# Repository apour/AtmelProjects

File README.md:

"# AtmelProjects" 
Zmena v souboru readme

Zmena vsouboru do master branch

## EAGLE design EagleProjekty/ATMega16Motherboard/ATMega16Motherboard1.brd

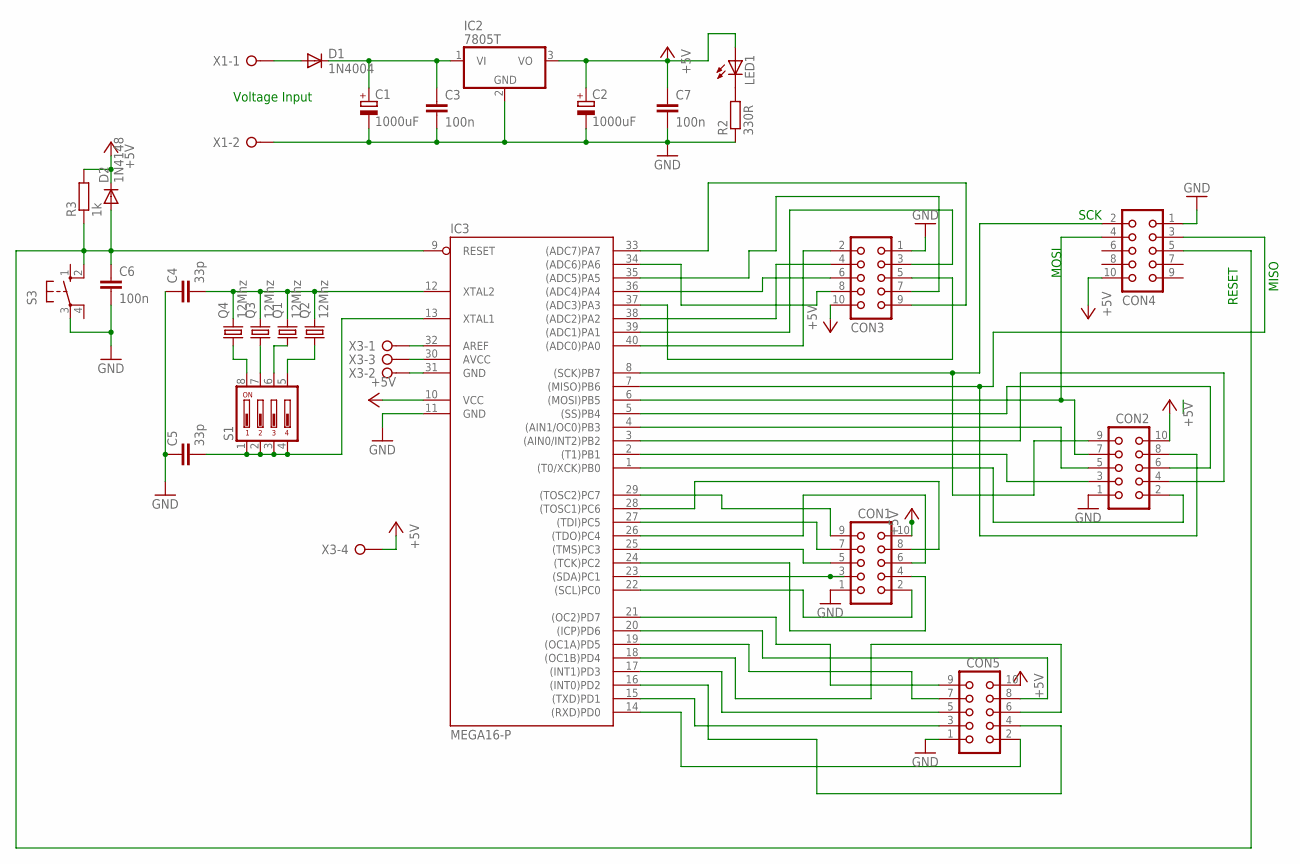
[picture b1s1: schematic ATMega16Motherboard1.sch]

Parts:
C1, C2: 1000uF; E2,5-7
C3, C6, C7: 100n; C025-024X044
C4, C5: 33p; C025-024X044
CON1, CON2, CON3, CON4, CON5: CON10
D1: 1N4004; DO41-10
D2: 1N4148; DO35-10
IC2: 7805T; TO220H
IC3: MEGA16-P; DIL40
LED1: LED5MM
Q1, Q2, Q3, Q4: 12Mhz; HC18U-V
R2: 330R; 0204/5
R3: 1k; 0204/5
S1: DIP04YL
S3: 10-XX; B3F-10XX
X1: W237-02P; W237-132
X3: W237-04P; W237-4P

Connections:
+5V: C2.+, C7.1, CON1.10, CON2.10, CON3.10, CON4.10, CON5.10, D2.C, IC2.3 (VO), IC3.10 (VCC), LED1.A, R3.2, X3.4
GND: C1.-, C2.-, C3.2, C4.1, C5.1, C6.2, C7.2, CON1.1, CON2.1, CON3.1, CON4.1, CON5.1, IC2.2 (GND), IC3.11 (GND), R2.1, S3.3, X1.2
unnamed: D1.A, X1.1
unnamed: C1.+, C3.1, D1.C, IC2.1 (VI)
unnamed: CON1.2, IC3.22 ((SCL)PC0)
unnamed: CON2.2, IC3.1 ((T0/XCK)PB0)
unnamed: CON2.3, IC3.2 ((T1)PB1)
unnamed: CON1.3, IC3.23 ((SDA)PC1)
unnamed: IC3.32 (AREF), X3.1
unnamed: CON2.4, IC3.3 ((AIN0/INT2)PB2)
unnamed: CON2.5, IC3.4 ((AIN1/OC0)PB3)
unnamed: CON2.6, IC3.5 ((SS)PB4)
unnamed: CON3.2, IC3.40 ((ADC0)PA0)
unnamed: IC3.30 (AVCC), X3.3
unnamed: IC3.31 (GND), X3.2
unnamed: Q4.1, S1.8
unnamed: Q3.1, S1.7
unnamed: Q1.1, S1.6
unnamed: Q2.1, S1.5
unnamed: CON3.3, IC3.39 ((ADC1)PA1)
unnamed: CON1.4, IC3.24 ((TCK)PC2)
unnamed: LED1.K (C), R2.2
unnamed: CON2.9, CON4.2, IC3.8 ((SCK)PB7)
unnamed: CON2.7, CON4.4, IC3.6 ((MOSI)PB5)
unnamed: CON2.8, CON4.3, IC3.7 ((MISO)PB6)
unnamed: CON5.7, IC3.19 ((OC1A)PD5)
unnamed: C5.2, IC3.13 (XTAL1), S1.1, S1.2, S1.3, S1.4
unnamed: C4.2, IC3.12 (XTAL2), Q1.2, Q2.2, Q3.2, Q4.2
unnamed: C6.1, CON4.5, D2.A, IC3.9 (RESET), R3.1, S3.2 (S1)
unnamed: CON3.4, IC3.38 ((ADC2)PA2)
unnamed: CON3.5, IC3.37 ((ADC3)PA3)
unnamed: CON3.6, IC3.36 ((ADC4)PA4)
unnamed: CON3.7, IC3.35 ((ADC5)PA5)
unnamed: CON3.8, IC3.34 ((ADC6)PA6)
unnamed: CON3.9, IC3.33 ((ADC7)PA7)
unnamed: CON1.5, IC3.25 ((TMS)PC3)
unnamed: CON1.6, IC3.26 ((TDO)PC4)
unnamed: CON1.7, IC3.27 ((TDI)PC5)
unnamed: CON1.8, IC3.28 ((TOSC1)PC6)
unnamed: CON1.9, IC3.29 ((TOSC2)PC7)
unnamed: CON5.9, IC3.21 ((OC2)PD7)
unnamed: CON5.8, IC3.20 ((ICP)PD6)
unnamed: CON5.6, IC3.18 ((OC1B)PD4)
unnamed: CON5.5, IC3.17 ((INT1)PD3)
unnamed: CON5.4, IC3.16 ((INT0)PD2)
unnamed: CON5.3, IC3.15 ((TXD)PD1)
unnamed: CON5.2, IC3.14 ((RXD)PD0)

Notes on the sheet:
SCK
MISO
MOSI
RESET
Voltage Input

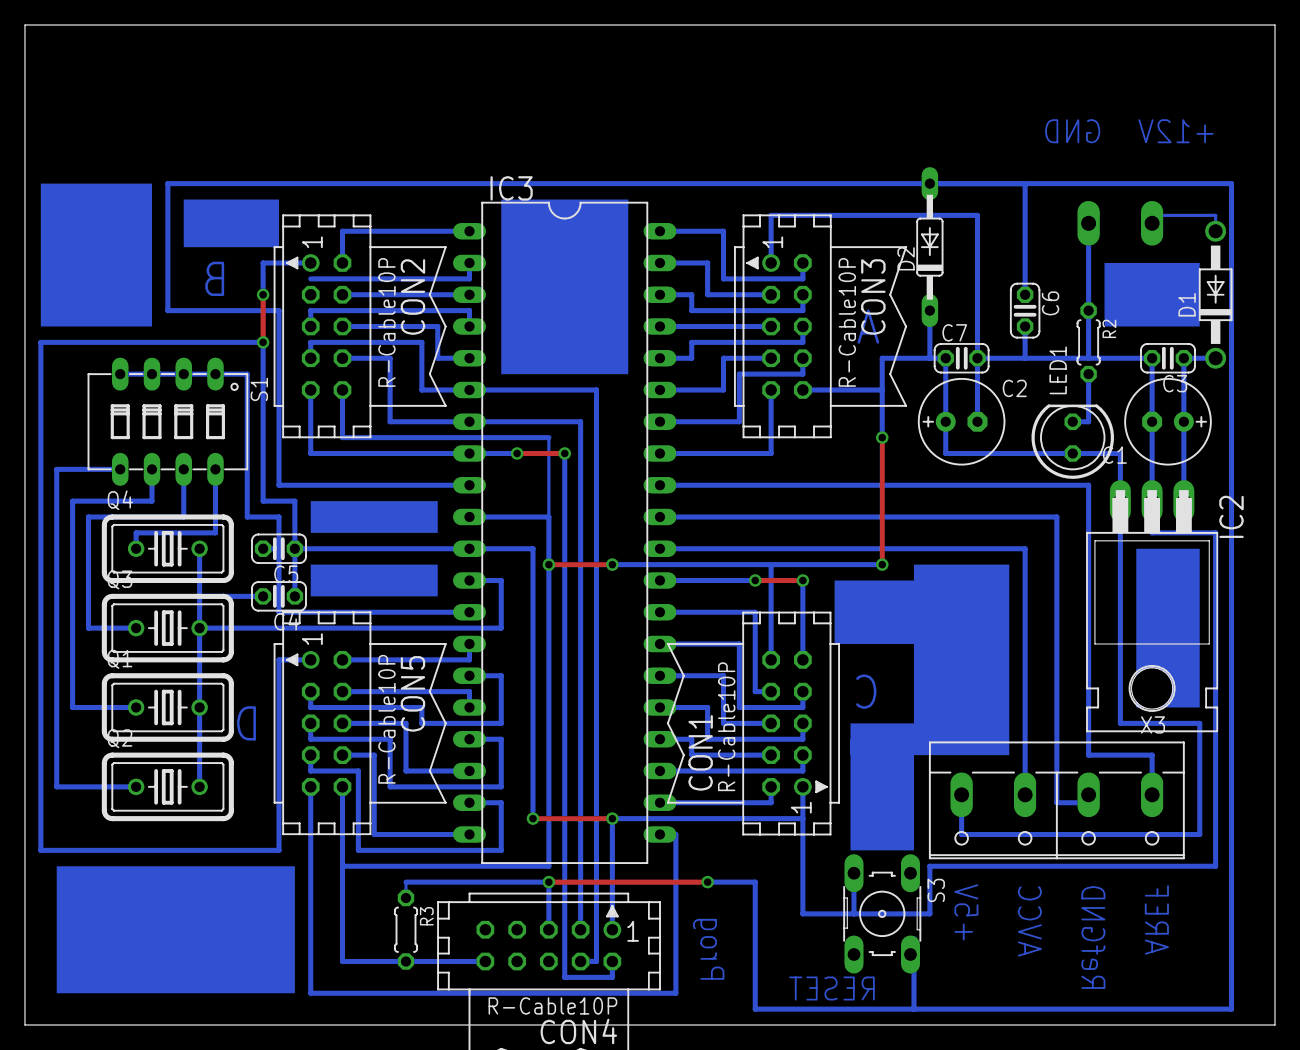
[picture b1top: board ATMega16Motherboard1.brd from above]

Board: 2 copper layers, 100.0 x 80.0 mm, 27 parts (1 on the bottom side), 47 nets.

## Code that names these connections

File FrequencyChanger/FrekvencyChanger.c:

/*
 * FrequencyChanger.c
 *
 * Created: 27.8.2022 18:13:48
 * Author: Ales
 *
 * MEASURE FREQUENCY ON PD3 (INT1) AND SEND INFO BY UART 19200 B
 * Input delta is set by voltage frequency on PIN PC1
 * Output Frequency is on PINT PC0
 * Output duty is on PC2
 * Input temp sensor by voltage on PIN PC4
 *
 * Must be connected
 * -----------------
 * AGND - Ground
 * AREF - +5V
 * AVCC - +5V
 * 
 *
 */ 

//#define __AVR_ATmega8__
#define F_CPU 12000000UL // Clock Speed

#include <avr/io.h>
#include <avr/interrupt.h>
#include <avr/delay.h>

#define ADJUST_VOLTAGE_FREQUENCY_INPUT_PIN				1
#define TEMPERATURE_SENSOR_VOLTAGE_INPUT_PIN			3
//#define DUMP_TO_UART									1
#define OUTPUT_DUTY_MIN									20
#define OUTPUT_DUTY_MAX									100
#define TEMPERATURE_SENSOR_MIN_VALUE					0x298

// counters
volatile unsigned int repeat_cnt1=0;
volatile unsigned int repeat_cnt2=0;

// measure input signal
volatile unsigned int measureFrc=0;
volatile unsigned int signalDetectorCounter=0;
volatile unsigned int lastSignalDetectorCounter=0;

// output signal
unsigned short outPinHi;
volatile unsigned int outSignalLimit=0;
volatile unsigned int signalOutCounter=0;
unsigned long deltaOutSignalLimit=0;

volatile unsigned short needChange = 0;
volatile unsigned short needCheck = 0;
	
void timer0Init()
   {
   // enable interrupt from timer 0 
   TIMSK = TIMSK | _BV(TOIE0);
   // set CLOCK / 64
   TCCR0 = _BV(CS01) | _BV(CS00);
   // set counter
   TCNT0 = 241;
   sei();
   }

void OutFrequenceChangeLogicLevel()
	{
	if (outPinHi==1)
		{
		PORTC&= ~_BV(PC0);	
		outPinHi=0;
		}		 
	else
		{
		PORTC|= _BV(PC0);
		outPinHi=1;
		}	   
	}			
      
SIGNAL(SIG_OVERFLOW0)
   {
   cli();
   // set counter
   TCNT0 = 241;
   signalDetectorCounter++;
   signalOutCounter++;
   
   if (signalOutCounter>outSignalLimit)
		{
		needChange = 1;
		signalOutCounter = 0;
	    } 
   sei();  
   }


SIGNAL(SIG_INTERRUPT1)
	{
	cli();
	needCheck = 1;
	sei();
	}	

static void hardwareInit(void)
{
    PORTD = 0xfa;   /* 1111 1010 bin: activate pull-ups except on USB lines */
    DDRD = 0x02;    /* 0000 0010 bin: remove USB reset condition */
	
    // set PC0 and PC2 as output
	DDRC = _BV(PC0) | _BV(PC2);
	PORTC = 0;
	
	// SET INT1 for input frequency
	PORTD|= _BV(PD3);
	// SET INT0 for input frequency temperature
	//PORTD|= _BV(PD2);
	
	// set PC0 and PC2 as output
	DDRC = _BV(PC0) | _BV(PC2);
	PORTC = 0;
	
	GICR |= _BV(INT1);	/* enable INT1 */
	//GICR |= _BV(INT0);	/* enable INT0 */
	MCUCR|= _BV(ISC11);
	MCUCR|= _BV(ISC01);

	sei();
}
	
int main(void)  
{
	hardwareInit();
	timer0Init();
	
	// test 
	outSignalLimit = 1000;
	lastSignalDetectorCounter = 1000;
	
	outPinHi = 0;
    sei();
	
	while (1)
		{
		if (needChange)
			{
			OutFrequenceChangeLogicLevel();
			needChange = 0;
			}
		
		if (needCheck)
			{
			needCheck = 0;
			outSignalLimit = signalDetectorCounter<<1;
			signalDetectorCounter=0;		
			if (signalOutCounter>outSignalLimit)
				{
				signalOutCounter = 0;
				needChange = 1;
				}
			}		
		}			
		
	return 1;
}	

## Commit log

2018-02-28 Pridana fotka
2018-02-28 Zmena v souboru
2018-02-28 Zkouska working branch
2018-02-28 dalsi zmena
2018-02-28 add pdf
2022-10-25 first binary file
2022-10-25 Frequency changer, not tested yet
2022-11-08 fsdfsd
2022-11-08 added test file
2022-11-12 Eagle projects
2022-11-13 AtMega 16 motherboard
2022-11-13 Update motherboard AT Mega 16
2022-12-25 78hc595 example#
